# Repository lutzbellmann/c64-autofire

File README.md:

# c64-autofire
Autofire Adapter for the Commodore 64 Control Ports

# Features
Dual Port, configurable Autofire Adapter for the C64 with any digital Joystick

- No external power supply; powered by the Commodore 64
- Tap on/ Tap off function
- no potis, no switches, 1 button control
- configurable for 4 different autofire speeds; 10Hz, 3,8Hz, 1,9Hz, 1,2Hz
- highly stable autofire frequency, due to hardware timers
- Port A and Port B fully independent
- fire button overrides autofire (f.e. load weapon *KATAKIS*)
- port functions fully retained; mouse or other appliances can be used without restrictions
- autofire speed for each port is retained for next power-up (saved to eeprom)
- autofire off on computer power-up (no more glitches due to forgotten Autofire switch ;-) )

# Installation
Schematics can be found in the respective folder. I added the PCB layout from KiCAD as well as the GERBER data. I am not proficient at this, so the GERBER data ma not be good enough for PCB manufacturing. Please check for yourself. Maybe, somebody can help.
Parts list:
- PCB
- Attiny45
- 2x BZX85 Diodes 5,6V or higher
- 2x 15nF ceramic capacitors
- 2x female DB9 connector
- 2x male DB9 connector

Housing:
I have put some FreeCAD files and STLs in the respective folder. Use at will, or make your own.

Flashing the Attiny:
- compatible flash programmer needed (f.e. STK500, TL866, Arduino like programmes,....)
- WARNING: flashing the Attiny will only work once with ISP programmers, since the Fuses are written to disable the Reset pin (PB5).
  For future programming/ reuse a high voltage programmer is needed.
- to compile the *.asm file, install AVRA with "sudo apt install avra"
- to flash using an STK500 or similar programmer, install AVRDUDE: "sudo apt install avrdude"

There are in general two options for programming:
1) - Use the Makefile to produce your own binaries and flash
Fix your directories and programmer in the Makefile.
To flash the chip and write the fuses, connect your programmer incl. Attiny and run:
sudo make install

2) - Use the HEX binaries included
You can flash the chip without compiling the assembly to binary by using the *.hex file provided.
To use AVR Dude in the directory with the hex file:
sudo avrdude -p t45 -P (your interface) -c (your programmer) -B 1024 -U flash:w:C64_autofire.hex

Then you have to burn the fuses with:

sudo $(AVRDUDE) -p t45 -P (your interface) -c (your programmer) -B 1024 -U lfuse:w:0xe2:m -U hfuse:w:0x57:m

For "your interface" choose the interface your programmer is connected to. F.e. /dev/ttyACM0 or COM3.
See detailed instructions for using AVRDUDE under https://linux.die.net/man/1/avrdude.

WARNING: check your circuit properly! Connection errors and short circuits could destroy your C64! No warranty is given for any usage
of this Autofire adapter. Do not try it, if you are not knowing what you are doing. Usage at your own risk!

# Usage
Plug in the autofire adapter carfully into the C64 Control Ports and switch on the computer.

Configuration of autofire speed:
- hold down config button for the respective port and tap the joystick button 1-4 times depending on the autofire speed you want.
1x -> very slow ... 4x -> very fast; after 1 sec speed is saved for that port
- activate autofire for the respective port by tapping the config button once
- tap again for deactivation

HAVE FUN

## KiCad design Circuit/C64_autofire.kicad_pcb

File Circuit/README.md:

This folder contains the schematic of the circuit and all related files.
Use KiCAD to view and edit the schematic.

More to come:
- PCB layout
- Parts list

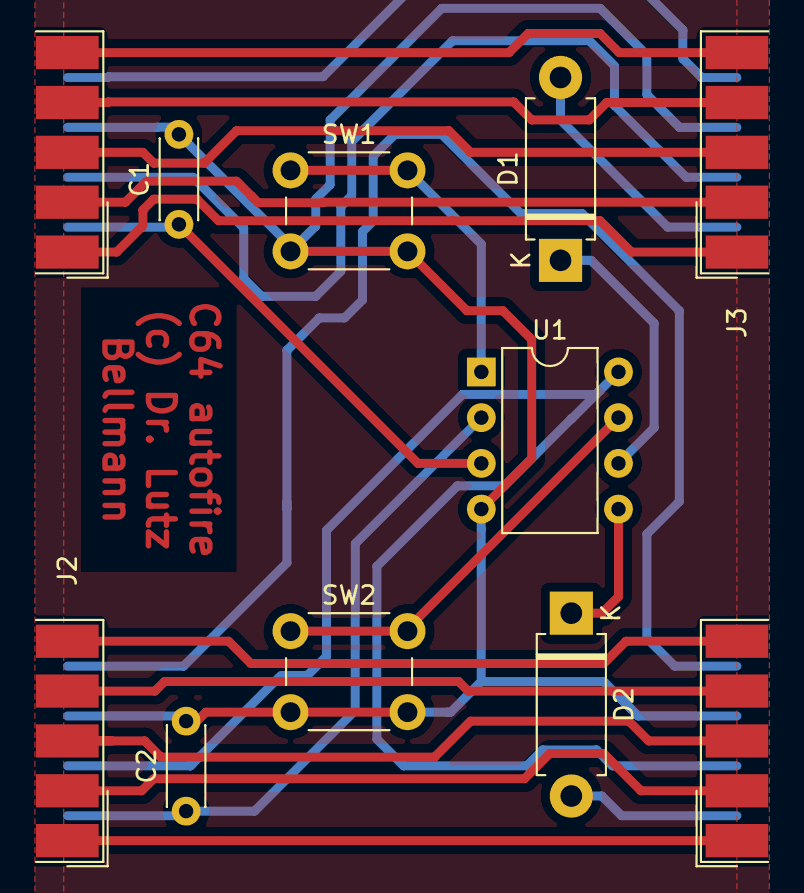
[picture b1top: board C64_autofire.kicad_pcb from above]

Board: 2 copper layers, 11 parts (0 on the bottom side), 23 nets.

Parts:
C1, C2: 15nF; C_Disc_D4.3mm_W1.9mm_P5.00mm
D1, D2: BZX85; 5,6V; D_DO-15_P10.16mm_Horizontal
J1: DB9_Female; JoyA; DSUB-9_Female_EdgeMount_P2.77mm
J2: DB9_Female; JoyB; DSUB-9_Female_EdgeMount_P2.77mm
J3: DB9_Male; PORTA; DSUB-9_Male_EdgeMount_P2.77mm
J4: DB9_Male; PORTB; DSUB-9_Male_EdgeMount_P2.77mm
SW1: SW_Push; PortA; SW_PUSH_6mm_H9.5mm
SW2: SW_Push; PortB; SW_PUSH_6mm_H9.5mm
U1: ATtiny45-20PU; DIP-8_W7.62mm

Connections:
unnamed: C1.1, J1.6, U1.3
unnamed: C1.2, C2.2, J1.8, J2.8, J3.8, J4.8, SW1.2, SW2.2, U1.4
unnamed: C2.1, J2.6, U1.2
unnamed: D1.1, U1.6
unnamed: D1.2, J3.6
unnamed: D2.1, U1.5
unnamed: D2.2, J4.6
unnamed: J1.1, J3.1
unnamed: J1.2, J3.2
unnamed: J1.3, J3.3
unnamed: J1.4, J3.4
unnamed: J1.5, J3.5
unnamed: J1.7, J3.7
unnamed: J1.9, J3.9
unnamed: J2.1, J4.1
unnamed: J2.2, J4.2
unnamed: J2.3, J4.3
unnamed: J2.4, J4.4
unnamed: J2.5, J4.5
unnamed: J2.7, J4.7, U1.8
unnamed: J2.9, J4.9
unnamed: SW1.1, U1.1
unnamed: SW2.1, U1.7

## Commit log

2019-12-23 Create blank
2019-12-23 FreeCAD and STL files for Autofire Adapter
2019-12-23 Schematic of Autofire Adapter
2019-12-23 Added first version of the manual
2019-12-30 GERBER Data and PCB layout added
    Warning! data has not been confirmed working. Experimental!
2019-12-30 updated instructions: installation; use of GERBER data
2019-12-30 corrections
